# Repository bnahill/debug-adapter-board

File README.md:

debug-adapter-board
===================

A simple board for interfacing different JTAG, SWD, and CC debug headers

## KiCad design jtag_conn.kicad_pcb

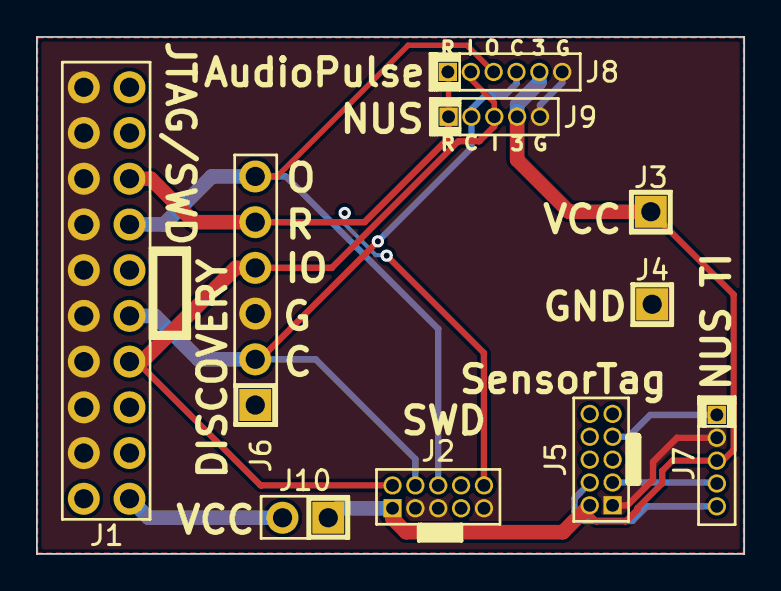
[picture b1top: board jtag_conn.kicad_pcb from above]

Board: 2 copper layers, 39.3 x 28.7 mm, 10 parts (0 on the bottom side), 10 nets.

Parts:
J1: CONN_10X2; HDR_10X2_100MIL_THRU
J2, J5: CONN_5X2; HDR_5X2_50MIL_THRU
J3, J4: CONN_1X1; HDR_1X1_100MIL_THRU
J6: CONN_6X1; HDR_6X1_100MIL_THRU
J7, J9: CONN_5X1; HDR_5X1_50MIL_THRU
J8: CONN_6X1; HDR_6X1_50MIL_THRU
J10: CONN_2X1; HDR_2X1_100MIL_THRU

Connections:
/GND: J1.4, J1.6, J1.8, J1.10, J1.12, J1.14, J1.16, J1.18, J1.20, J2.3, J2.5, J2.9, J4.1, J5.1, J6.3, J7.2, J8.6, J9.5
/RESET: J1.15, J2.10, J6.5, J8.1, J9.1
/SWCLK_TCLK: J1.9, J2.4, J6.2, J8.4, J9.2
/SWDIO_TMS: J1.7, J2.2, J6.4, J8.2, J9.3
/SWO_TDO: J1.13, J2.6, J6.6, J8.3
/TI_DC: J5.3, J7.4
/TI_DD: J5.4, J7.5
/TI_RESET: J5.7, J7.1
/VCC: J2.1, J3.1, J5.2, J7.3, J8.5, J9.4, J10.1
/VCC_JTAG: J1.1, J10.2

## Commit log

2014-02-05 Added schematic and most of PCB
2015-01-01 Printed r1a
